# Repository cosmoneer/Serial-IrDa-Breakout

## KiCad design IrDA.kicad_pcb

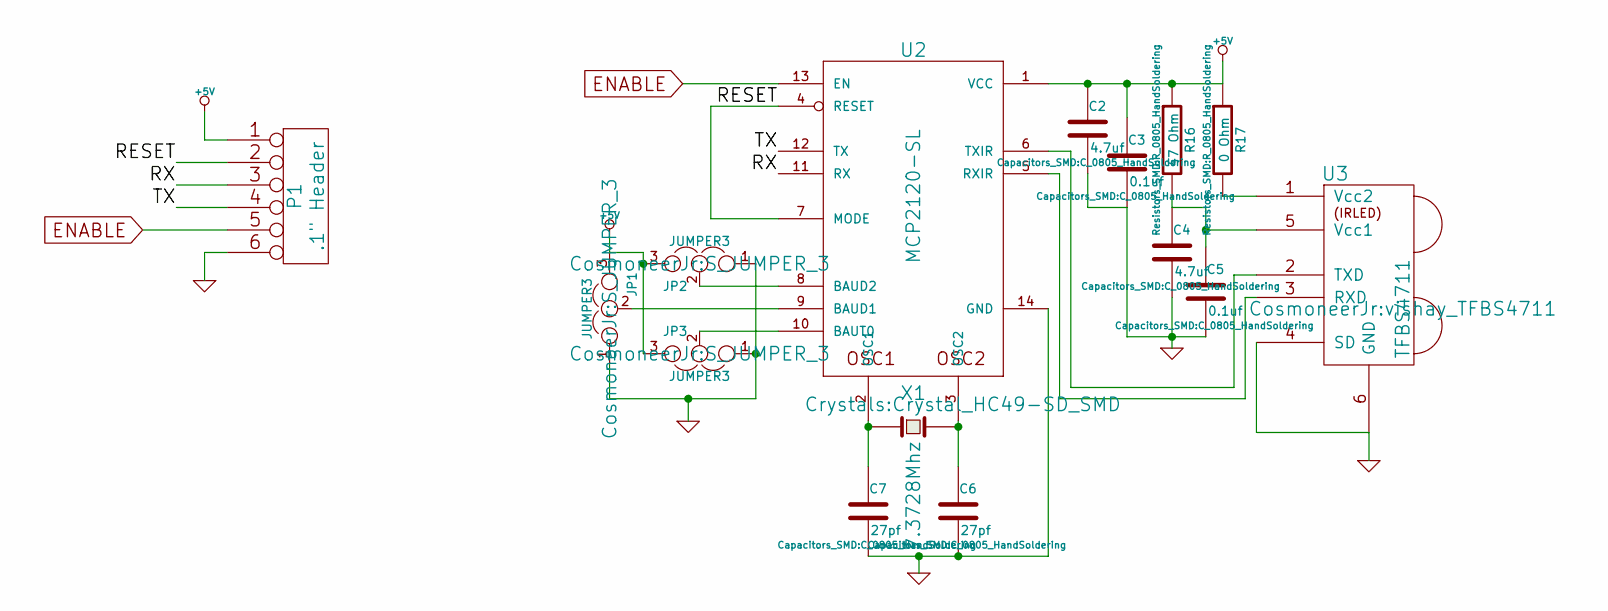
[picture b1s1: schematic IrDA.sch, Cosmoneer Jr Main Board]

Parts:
C2, C4: 4.7uf; C_0805_HandSoldering
C3, C5: 0.1uf; C_0805_HandSoldering
C6, C7: 27pf; C_0805_HandSoldering
JP1, JP2, JP3: JUMPER3; S_JUMPER_3
P1: .1\" Header; Pin_Header_Straight_1x06
R16: 47 Ohm; R_0805_HandSoldering
R17: 0 Ohm; R_0805_HandSoldering
U2: MCP2120-SL; SOIC-14_N
U3: TFBS4711; vishay_TFBS4711
X1: 7.3728Mhz; Crystal_HC49-SD_SMD

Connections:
+5V: C2.1, C3.1, JP1.3, JP2.3, JP3.3, P1.1, R16.1, R17.1, U2.1 (VCC)
/RESET: P1.2, U2.4 (RESET), U2.7 (MODE)
/RX: P1.3, U2.11 (RX)
/TX: P1.4, U2.12 (TX)
ENABLE: P1.5, U2.13 (EN)
GND: C2.2, C3.2, C4.2, C5.2, C6.2, C7.2, JP1.1, JP2.1, JP3.1, P1.6, U2.14 (GND), U3.4 (SD), U3.6 (GND)
unnamed: C4.1, C5.1, R16.2, U3.5 (Vcc1)
unnamed: C6.1, U2.3 (OSC2), X1.2
unnamed: C7.1, U2.2 (OSC1), X1.1
unnamed: JP1.2, U2.9 (BAUD1)
unnamed: JP2.2, U2.8 (BAUD2)
unnamed: JP3.2, U2.10 (BAUT0)
unnamed: R17.2, U3.1 (Vcc2)
unnamed: U2.5 (RXIR), U3.3 (RXD)
unnamed: U2.6 (TXIR), U3.2 (TXD)

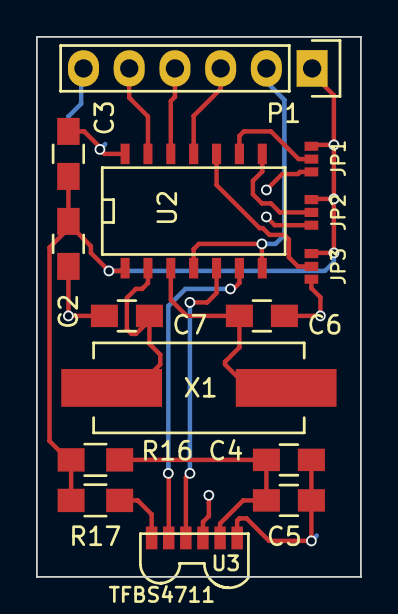
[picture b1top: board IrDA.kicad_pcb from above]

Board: 2 copper layers, 18.0 x 30.0 mm, 15 parts (0 on the bottom side), 15 nets.

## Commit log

2016-09-19 :octocat: Added .gitattributes & .gitignore files
2016-09-19 Prototype
    Initial Prototype Design
